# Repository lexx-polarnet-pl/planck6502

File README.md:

# Planck/Lexx W65C02 computer

My custom build of the W65C02 computer, based mostly on the [Planck6502](https://planck6502.com/) hardware design along with several new add-ons.
The firmware has been written entirely from scratch and does not use any of the original Planck code.

The system features a simple DOS-like environment that uses a single CompactFlash (CF) card formatted with a FAT16 partition for storage, enabling seamless file exchange with modern PCs. From the DOS prompt, the user can launch a BASIC interpreter, run a machine-language monitor, or execute custom applications written for the system—much like in MS-DOS.

From a hardware perspective, the computer is equipped with a Pico 2-based video card capable of driving a 640x480 video output with 256 colors. It emulates a VT100 terminal with ANSI color support and provides an 80x30 text mode very similar to standard VGA. The system also features an audio card equipped with a 4-channel, 8-bit DAC for stereo PCM playback, as well as a Yamaha OPL2 chip for FM synthesis.

Mass storage is handled via CF cards, and the base memory (32 KB RAM) is expandable via memory banking. User interaction is supported through standard PS/2 keyboard and mouse interfaces, and an onboard serial interface provides full terminal access as well as file transfer capability.

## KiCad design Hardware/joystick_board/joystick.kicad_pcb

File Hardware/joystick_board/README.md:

## Planck 6502 Joystick Interface

This is the dual joystick interface card for the Planck 6502 computer.

This is an entirely new build, not based on any existing board from the original Planck project.

## Revision History

| Version | Status | Changes |
| :---: | :---: | :--- |
| **1.0** | Under construction | Initial design |

**This board is a work in progress.**

This card aims to be a simple interface between joysticks and the 6502 CPU. The design supports standard Atari DB9 joysticks, extended to support dual fire buttons. The card also features built-in ESD protection.

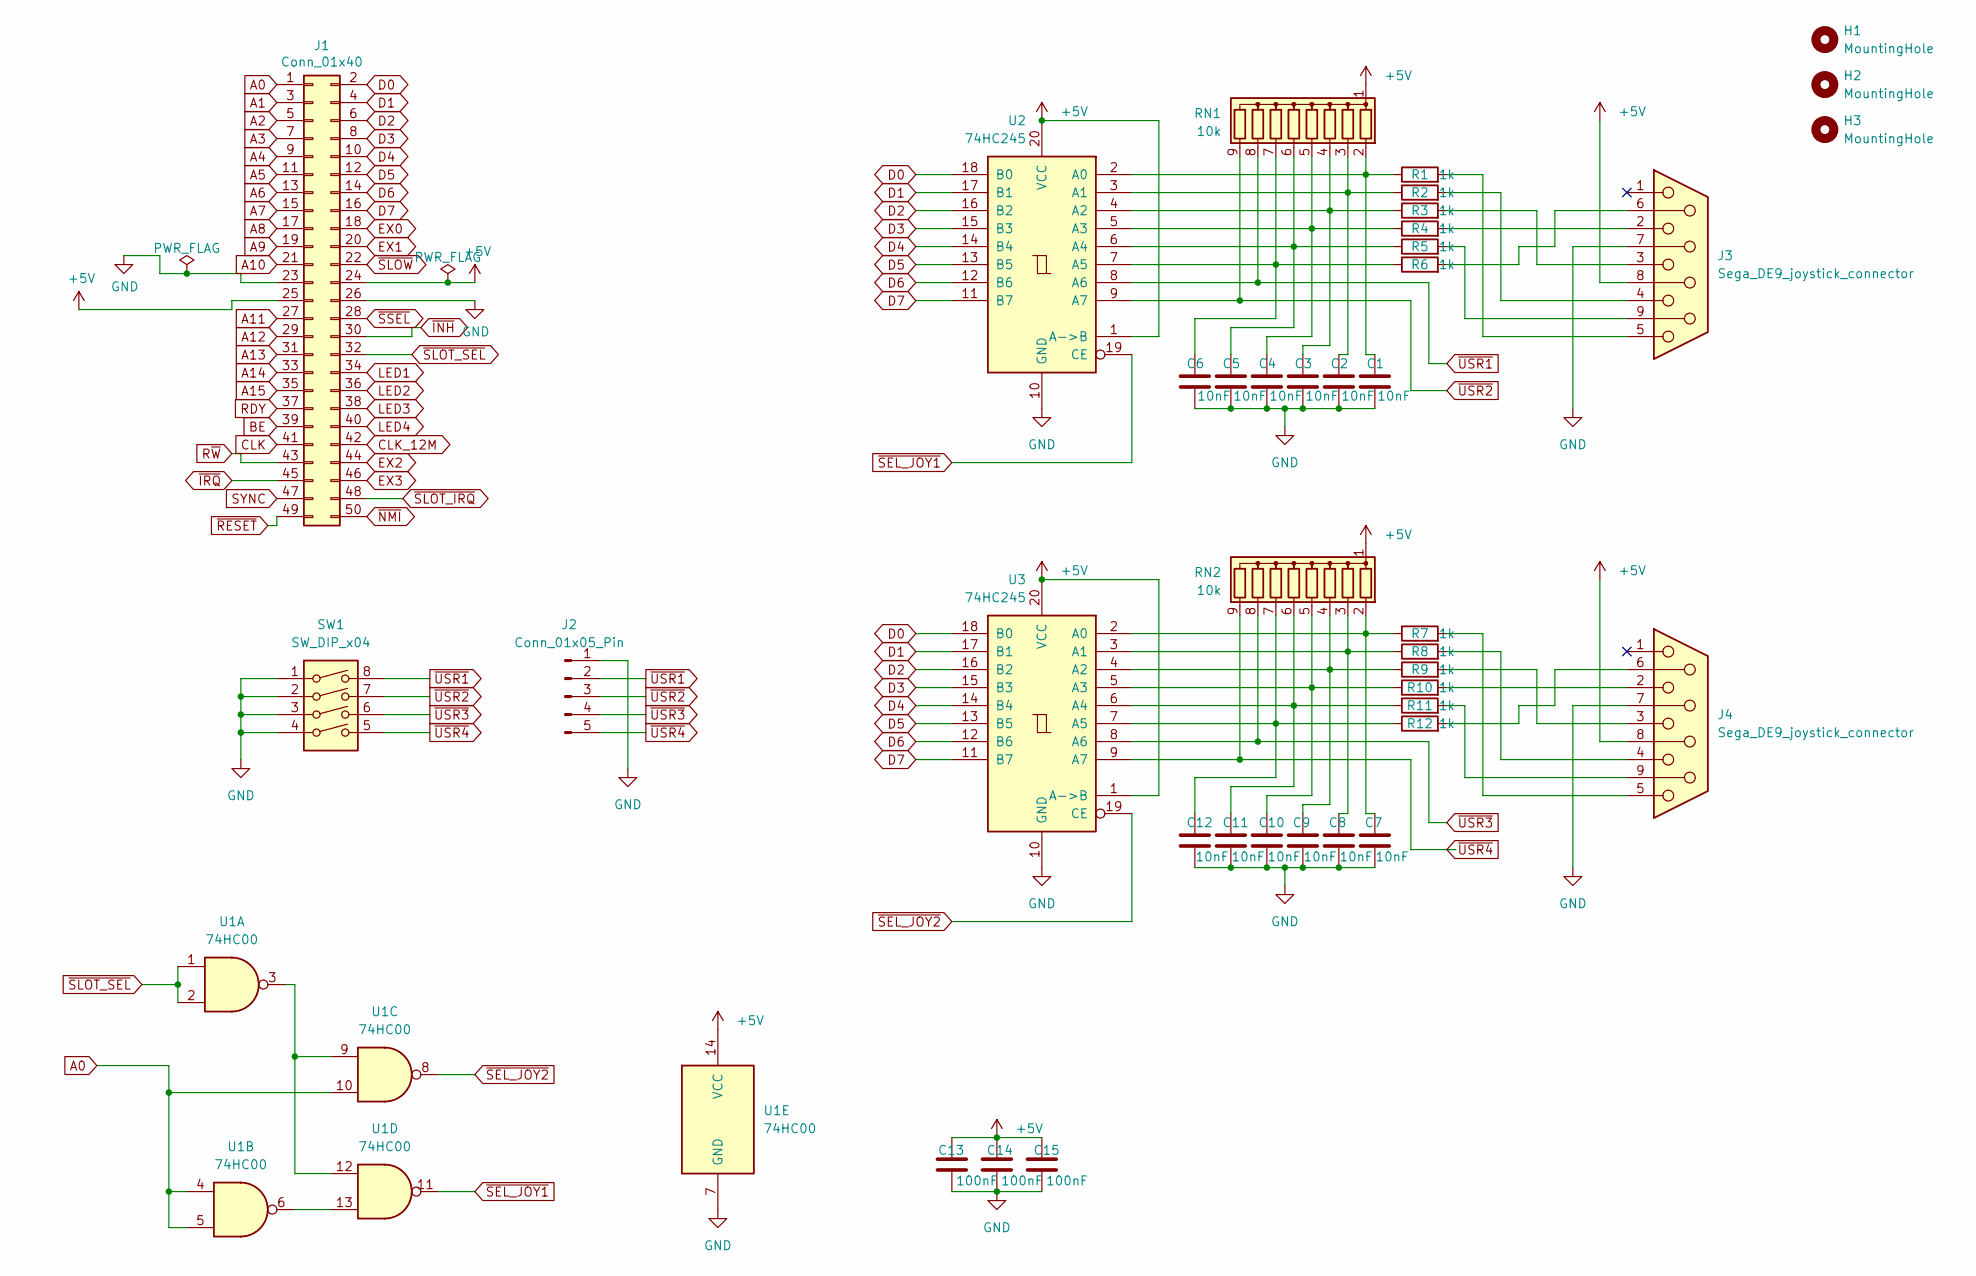
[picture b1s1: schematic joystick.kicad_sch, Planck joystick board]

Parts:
C1, C2, C3, C4, C5, C6, C7, C8, C9, C10, C11, C12: 10nF; C_Disc_D5.0mm_W2.5mm_P5.00mm
C13, C14, C15: 100nF; C_Disc_D5.0mm_W2.5mm_P5.00mm
H1, H2, H3: MountingHole; MountingHole_3.2mm_M3
J1: Conn_01x40; PinHeader_2x25_P2.54mm_Horizontal
J2: Conn_01x05_Pin; PinHeader_1x05_P2.54mm_Vertical
J3, J4: Sega_DE9_joystick_connector; Sega DE9 joystick connector
R1, R2, R3, R4, R5, R6, R7, R8, R9, R10, R11, R12: 1k; R_Axial_DIN0207_L6.3mm_D2.5mm_P2.54mm_Vertical
RN1, RN2: 10k; R_Array_SIP9
SW1: SW_DIP_x04; SW_DIP_SPSTx04_Piano_CTS_Series194-4MSTN_W7.62mm_P2.54mm
U1: 74HC00; DIP-14_W7.62mm_Socket
U2, U3: 74HC245; DIP-20_W7.62mm_Socket

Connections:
+5V: C13.1, C14.1, C15.1, J1.24, J1.25, J3.8, J4.8, RN1.1 (common), RN2.1 (common), U1.14 (VCC), U2.1 (A->B), U2.20 (VCC), U3.1 (A->B), U3.20 (VCC)
A0: J1.1, U1.4, U1.5, U1.10
A1: J1.3
A2: J1.5
A3: J1.7
A4: J1.9
A5: J1.11
A6: J1.13
A7: J1.15
A8: J1.17
A9: J1.19
A10: J1.21
A11: J1.27
A12: J1.29
A13: J1.31
A14: J1.33
A15: J1.35
BE: J1.39
CLK: J1.41
CLK_12M: J1.42
D0: J1.2, U2.18 (B0), U3.18 (B0)
D1: J1.4, U2.17 (B1), U3.17 (B1)
D2: J1.6, U2.16 (B2), U3.16 (B2)
D3: J1.8, U2.15 (B3), U3.15 (B3)
D4: J1.10, U2.14 (B4), U3.14 (B4)
D5: J1.12, U2.13 (B5), U3.13 (B5)
D6: J1.14, U2.12 (B6), U3.12 (B6)
D7: J1.16, U2.11 (B7), U3.11 (B7)
EX0: J1.18
EX1: J1.20
EX2: J1.44
EX3: J1.46
GND: C1.2, C2.2, C3.2, C4.2, C5.2, C6.2, C7.2, C8.2, C9.2, C10.2, C11.2, C12.2, C13.2, C14.2, C15.2, J1.23, J1.26, J2.1, J3.7, J4.7, SW1.1, SW1.2, SW1.3, SW1.4, U1.7 (GND), U2.10 (GND), U3.10 (GND)
LED1: J1.34
LED2: J1.36
LED3: J1.38
LED4: J1.40
unnamed: J3.2, R4.2
unnamed: J3.3, R3.2
unnamed: J3.4, R2.2
unnamed: J3.5, R1.2
unnamed: J3.6, R6.2
unnamed: J3.9, R5.2
unnamed: J4.2, R10.2
unnamed: J4.3, R9.2
unnamed: J4.4, R8.2
unnamed: J4.5, R7.2
unnamed: J4.6, R12.2
unnamed: J4.9, R11.2
unnamed: C1.1, R1.1, RN1.2 (R1), U2.2 (A0)
unnamed: C2.1, R2.1, RN1.3 (R2), U2.3 (A1)
unnamed: C3.1, R3.1, RN1.4 (R3), U2.4 (A2)
unnamed: C4.1, R4.1, RN1.5 (R4), U2.5 (A3)
unnamed: C5.1, R5.1, RN1.6 (R5), U2.6 (A4)
unnamed: C6.1, R6.1, RN1.7 (R6), U2.7 (A5)
unnamed: C7.1, R7.1, RN2.2 (R1), U3.2 (A0)
unnamed: C8.1, R8.1, RN2.3 (R2), U3.3 (A1)
unnamed: C9.1, R9.1, RN2.4 (R3), U3.4 (A2)
unnamed: C10.1, R10.1, RN2.5 (R4), U3.5 (A3)
unnamed: C11.1, R11.1, RN2.6 (R5), U3.6 (A4)
unnamed: C12.1, R12.1, RN2.7 (R6), U3.7 (A5)
unnamed: U1.3, U1.9, U1.12
unnamed: U1.6, U1.13
RDY: J1.37
R~W: J1.43
SYNC: J1.47
~INH: J1.30
~IRQ: J1.45
~NMI: J1.50
~RESET: J1.49
~SEL_JOY1: U1.11, U2.19 (CE)
~SEL_JOY2: U1.8, U3.19 (CE)
~SLOT_IRQ: J1.48
~SLOT_SEL: J1.32, U1.1, U1.2
~SLOW: J1.22
~SSEL: J1.28
~USR1: J2.2, RN1.8 (R7), SW1.8, U2.8 (A6)
~USR2: J2.3, RN1.9 (R8), SW1.7, U2.9 (A7)
~USR3: J2.4, RN2.8 (R7), SW1.6, U3.8 (A6)
~USR4: J2.5, RN2.9 (R8), SW1.5, U3.9 (A7)

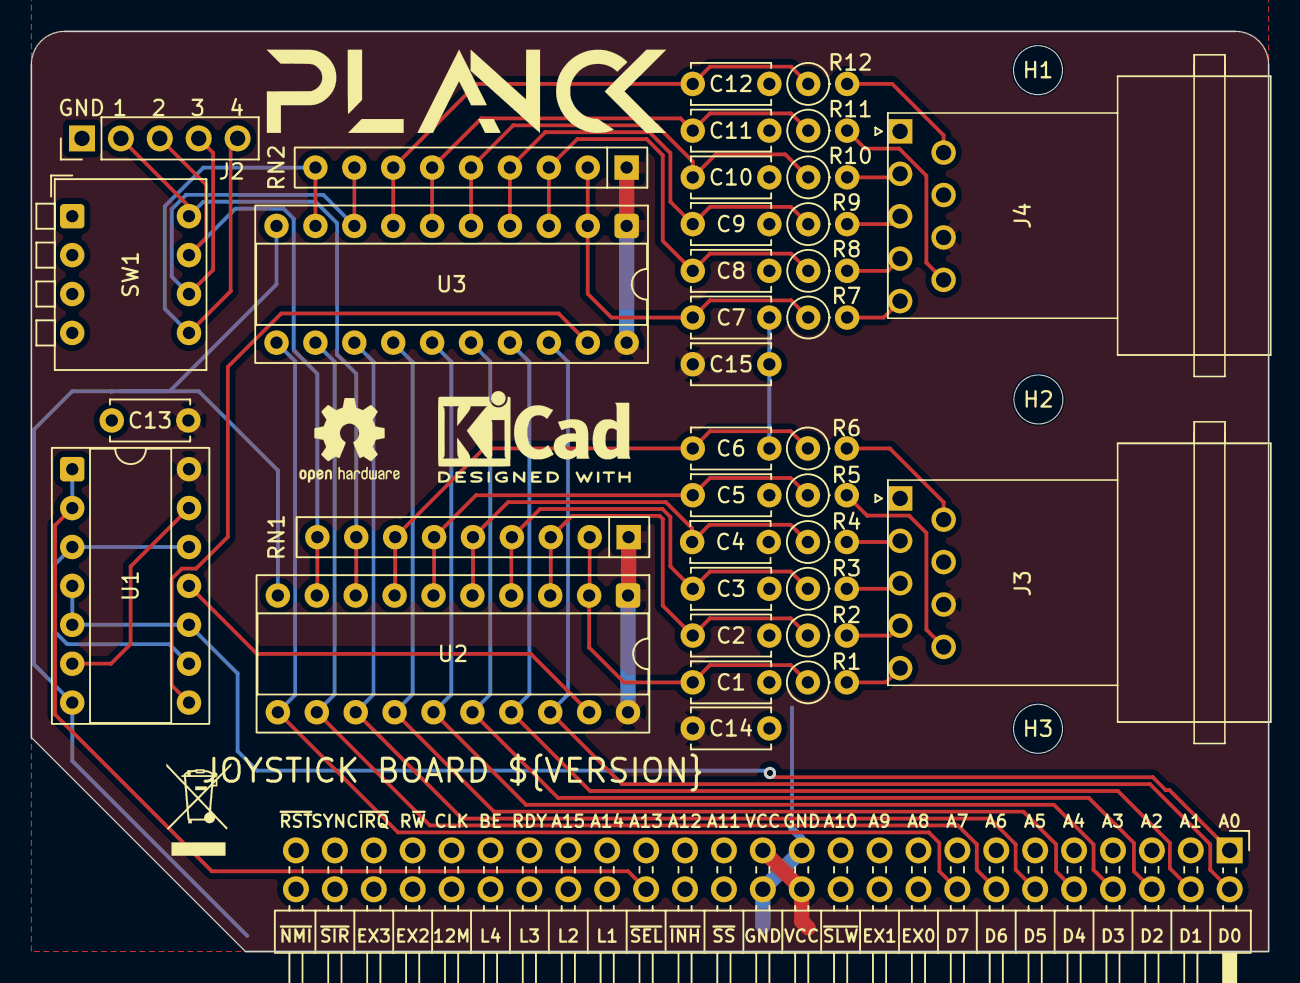
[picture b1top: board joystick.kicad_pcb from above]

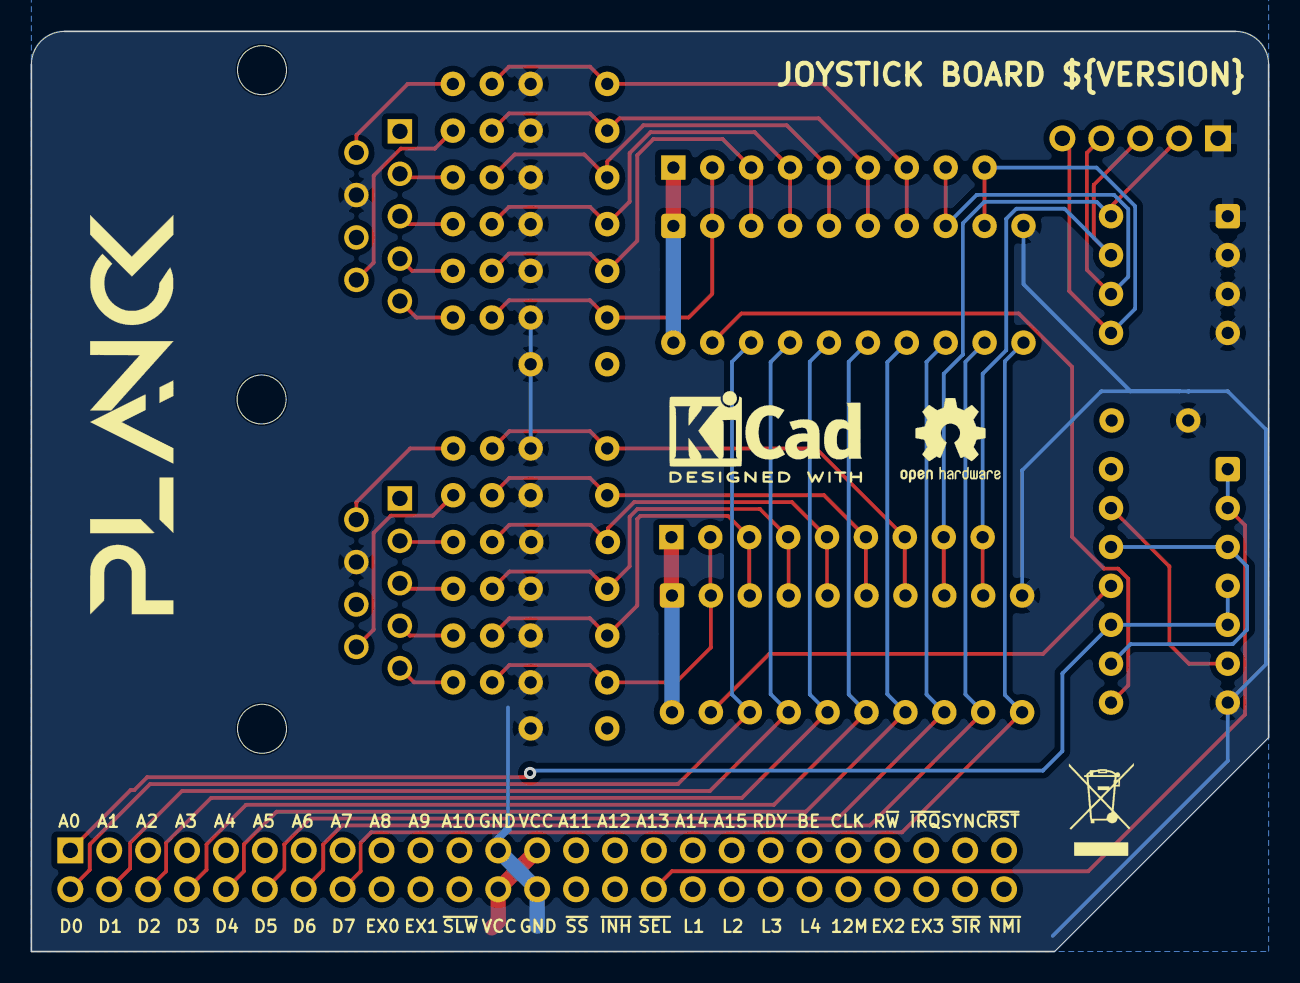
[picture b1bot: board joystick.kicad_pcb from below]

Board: 2 copper layers, 80.8 x 60.1 mm, 48 parts (4 on the bottom side), 44 nets.

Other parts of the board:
KICADLOGO1, KICADLOGO2: KiCad-Logo2_5mm_SilkScreen
LOGO1, LOGO2: LOGO; logo
OPENHARDWARE1, OPENHARDWARE2: OSHW-Logo2_7.3x6mm_SilkScreen
WASTE1, WASTE2: WEEE-Logo_4.2x6mm_SilkScreen

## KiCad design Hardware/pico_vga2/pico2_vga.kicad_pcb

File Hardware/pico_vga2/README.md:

## Planck 6502 Pico 2 VGA Board 

This is a VGA board for the Planck 6502 computer, based on the Raspberry Pi Pico 2. 

> [!CAUTION]
> **Compatibility Warning:**  
> This version is **not** compatible with the 1st generation Pico, as it is not 5V tolerant. **Use the Pico 2 only**, otherwise you risk damaging the board.

Compared to the original design, this card was rebuilt from scratch to achieve three main goals:
1. **PicoVGA Compatibility:** The pinout and resistor ladder match the [PicoVGA cmake](https://github.com/codaris/picovga-cmake) project, making the library as simple as possible to use.
2. **Hardware RDY Latch:** Implemented to give the Pico enough time to read, process, and respond to the W65C02 CPU by utilizing the RDY signal to pause the CPU when needed.
3. **Optimized Bus Routing:** The Address and Data bus pinout order was reversed to enable faster and more efficient bus operations on the Pico. 

Additionally, by leveraging the Pico 2, SMD level shifters were removed, leaving only a single THT bus buffer on the PCB. As a result, the entire board can now be soldered using strictly Through-Hole (THT) components.

## Revision History

| Version | Status | Changes |
| :---: | :---: | :--- |
| **1.0** | Work in progress | Initial design |

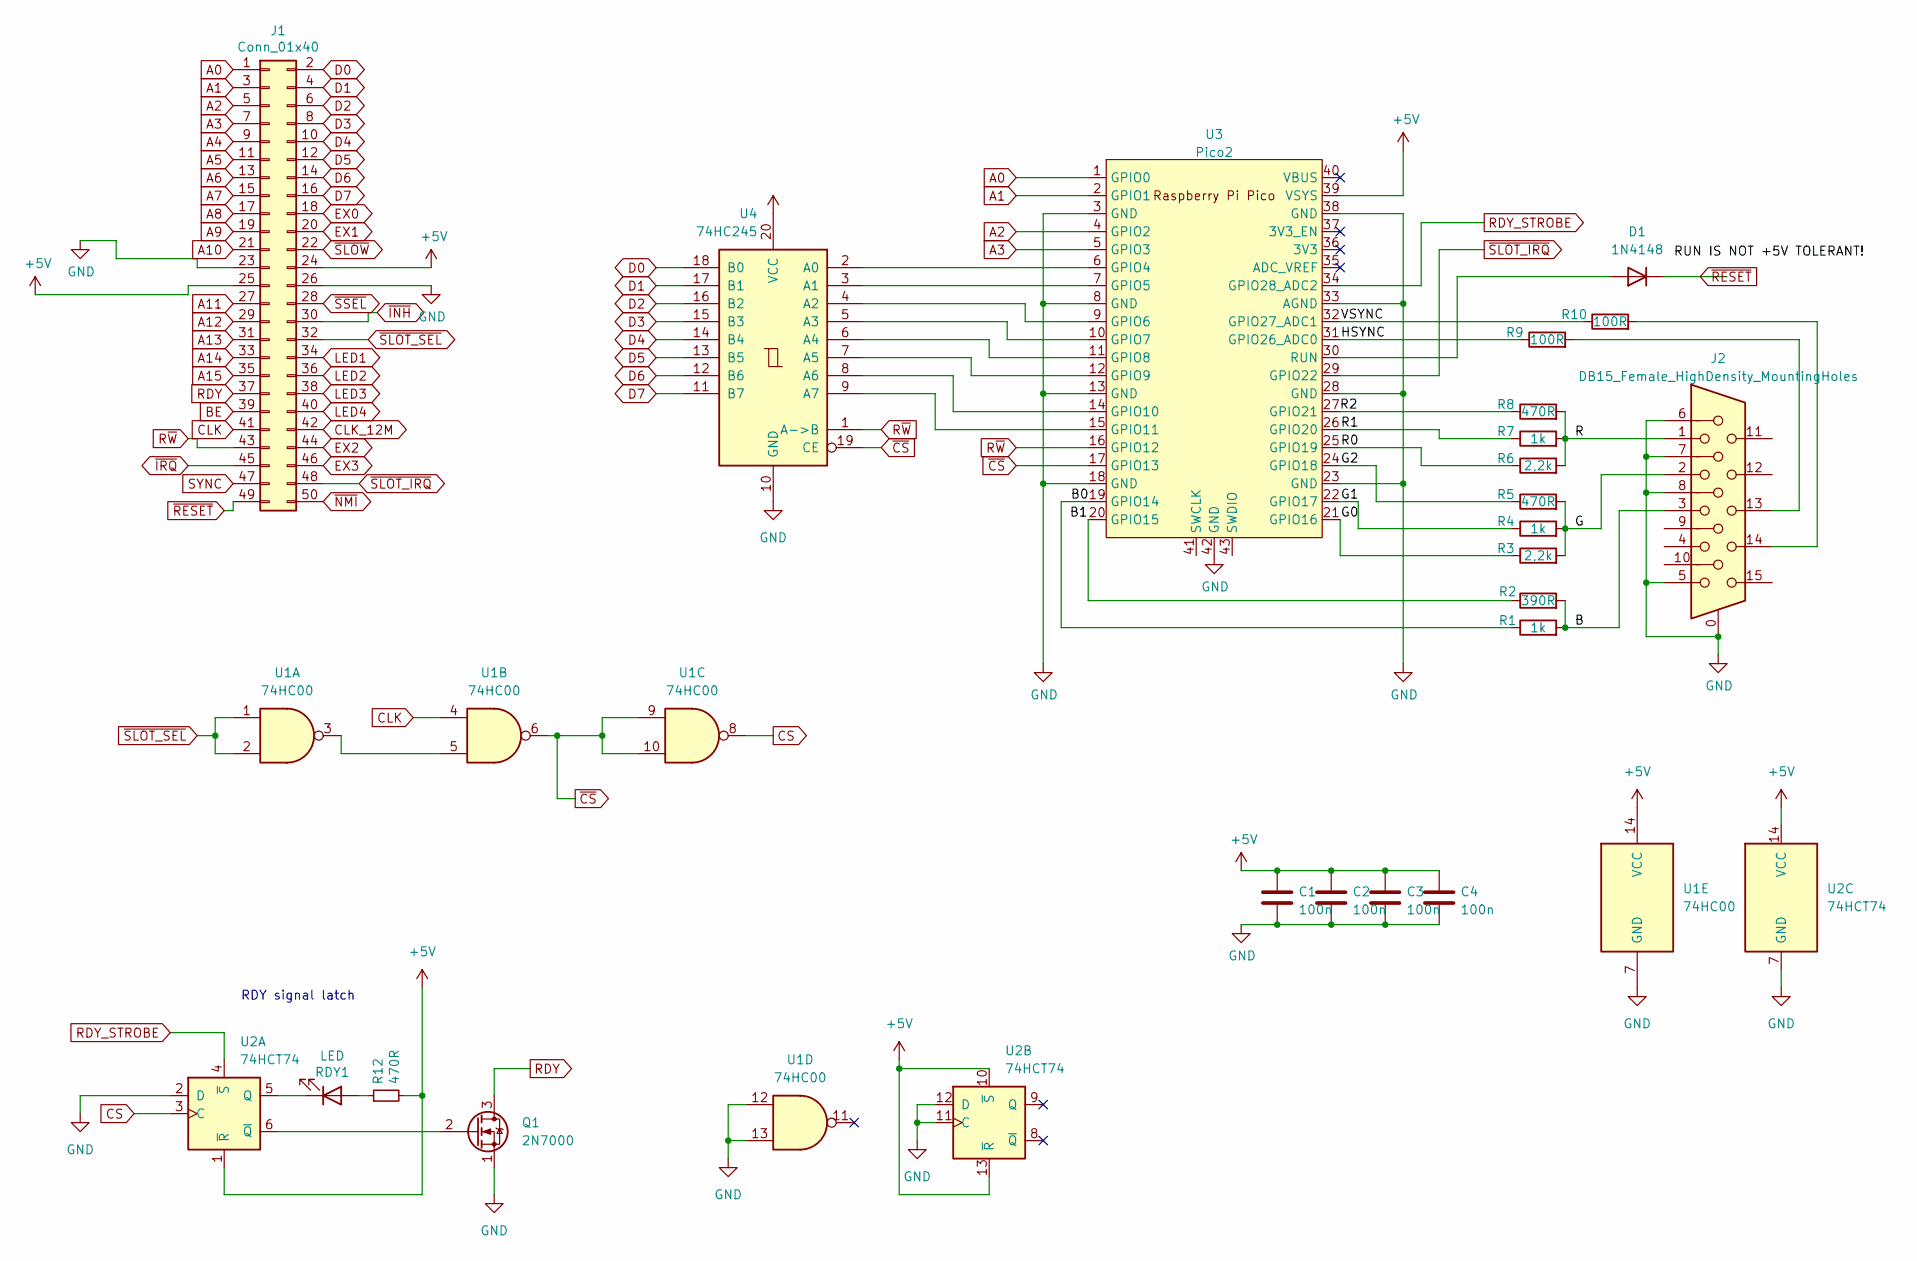
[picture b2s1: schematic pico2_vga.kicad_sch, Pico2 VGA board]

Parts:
C1, C2, C3, C4: 100n; C_Disc_D5.0mm_W2.5mm_P5.00mm
D1: 1N4148; D_DO-35_SOD27_P7.62mm_Horizontal
J1: Conn_01x40; PinHeader_2x25_P2.54mm_Horizontal
J2: DB15_Female_HighDensity_MountingHoles; DSUB-15-HD_Socket_Horizontal_P2.29x1.90mm_EdgePinOffset3.03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
Q1: 2N7000; TO-92_Inline
R1, R4, R7: 1k; R_Axial_DIN0309_L9.0mm_D3.2mm_P2.54mm_Vertical
R2: 390R; R_Axial_DIN0309_L9.0mm_D3.2mm_P2.54mm_Vertical
R3, R6: 2,2k; R_Axial_DIN0309_L9.0mm_D3.2mm_P2.54mm_Vertical
R5, R8: 470R; R_Axial_DIN0309_L9.0mm_D3.2mm_P2.54mm_Vertical
R9, R10: 100R; R_Axial_DIN0309_L9.0mm_D3.2mm_P2.54mm_Vertical
R12: 470R; R_Axial_DIN0207_L6.3mm_D2.5mm_P10.16mm_Horizontal
RDY1: LED; LED_D3.0mm
U1: 74HC00; DIP-14_W7.62mm_Socket
U2: 74HCT74; DIP-14_W7.62mm_Socket
U3: Pico2; RPi_Pico_SMD_TH
U4: 74HC245; DIP-20_W7.62mm_Socket

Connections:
+5V: C1.1, C2.1, C3.1, C4.1, J1.24, J1.25, R12.2, U1.14 (VCC), U2.1 (~R), U2.10 (~S), U2.13 (~R), U2.14 (VCC), U3.39 (VSYS), U4.20 (VCC)
/B: J2.3, R1.2, R2.2
/B0: R1.1, U3.19 (GPIO14)
/B1: R2.1, U3.20 (GPIO15)
/G: J2.2, R3.2, R4.2, R5.2
/G0: R3.1, U3.21 (GPIO16)
/G1: R4.1, U3.22 (GPIO17)
/G2: R5.1, U3.24 (GPIO18)
/HSYNC: R9.1, U3.31 (GPIO26_ADC0)
/R: J2.1, R6.2, R7.2, R8.2
/R0: R6.1, U3.25 (GPIO19)
/R1: R7.1, U3.26 (GPIO20)
/R2: R8.1, U3.27 (GPIO21)
/VSYNC: R10.1, U3.32 (GPIO27_ADC1)
A0: J1.1, U3.1 (GPIO0)
A1: J1.3, U3.2 (GPIO1)
A2: J1.5, U3.4 (GPIO2)
A3: J1.7, U3.5 (GPIO3)
A4: J1.9
A5: J1.11
A6: J1.13
A7: J1.15
A8: J1.17
A9: J1.19
A10: J1.21
A11: J1.27
A12: J1.29
A13: J1.31
A14: J1.33
A15: J1.35
BE: J1.39
CLK: J1.41, U1.4
CLK_12M: J1.42
CS: U1.8, U2.3 (C)
D0: J1.2, U4.18 (B0)
D1: J1.4, U4.17 (B1)
D2: J1.6, U4.16 (B2)
D3: J1.8, U4.15 (B3)
D4: J1.10, U4.14 (B4)
D5: J1.12, U4.13 (B5)
D6: J1.14, U4.12 (B6)
D7: J1.16, U4.11 (B7)
EX0: J1.18
EX1: J1.20
EX2: J1.44
EX3: J1.46
GND: C1.2, C2.2, C3.2, C4.2, J1.23, J1.26, J2.0, J2.5, J2.6, J2.7, J2.8, Q1.1 (S), U1.7 (GND), U1.12, U1.13, U2.2 (D), U2.7 (GND), U2.11 (C), U2.12 (D), U3.3 (GND), U3.8 (GND), U3.13 (GND), U3.18 (GND), U3.23 (GND), U3.28 (GND), U3.33 (AGND), U3.38 (GND), U3.42 (GND), U4.10 (GND)
LED1: J1.34
LED2: J1.36
LED3: J1.38
LED4: J1.40
unnamed: D1.2 (A), U3.30 (RUN)
unnamed: J2.13, R9.2
unnamed: J2.14, R10.2
unnamed: Q1.2 (G), U2.6 (~Q)
unnamed: R12.1, RDY1.2 (A)
unnamed: RDY1.1 (K), U2.5 (Q)
unnamed: U1.3, U1.5
unnamed: U3.6 (GPIO4), U4.2 (A0)
unnamed: U3.7 (GPIO5), U4.3 (A1)
unnamed: U3.9 (GPIO6), U4.4 (A2)
unnamed: U3.10 (GPIO7), U4.5 (A3)
unnamed: U3.11 (GPIO8), U4.6 (A4)
unnamed: U3.12 (GPIO9), U4.7 (A5)
unnamed: U3.14 (GPIO10), U4.8 (A6)
unnamed: U3.15 (GPIO11), U4.9 (A7)
RDY: J1.37, Q1.3 (D)
RDY_STROBE: U2.4 (~S), U3.34 (GPIO28_ADC2)
R~W: J1.43, U3.16 (GPIO12), U4.1 (A->B)
SYNC: J1.47
~CS: U1.6, U1.9, U1.10, U3.17 (GPIO13), U4.19 (CE)
~INH: J1.30
~IRQ: J1.45
~NMI: J1.50
~RESET: D1.1 (K), J1.49
~SLOT_IRQ: J1.48, U3.29 (GPIO22)
~SLOT_SEL: J1.32, U1.1, U1.2
~SLOW: J1.22
~SSEL: J1.28

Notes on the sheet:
RDY signal latch

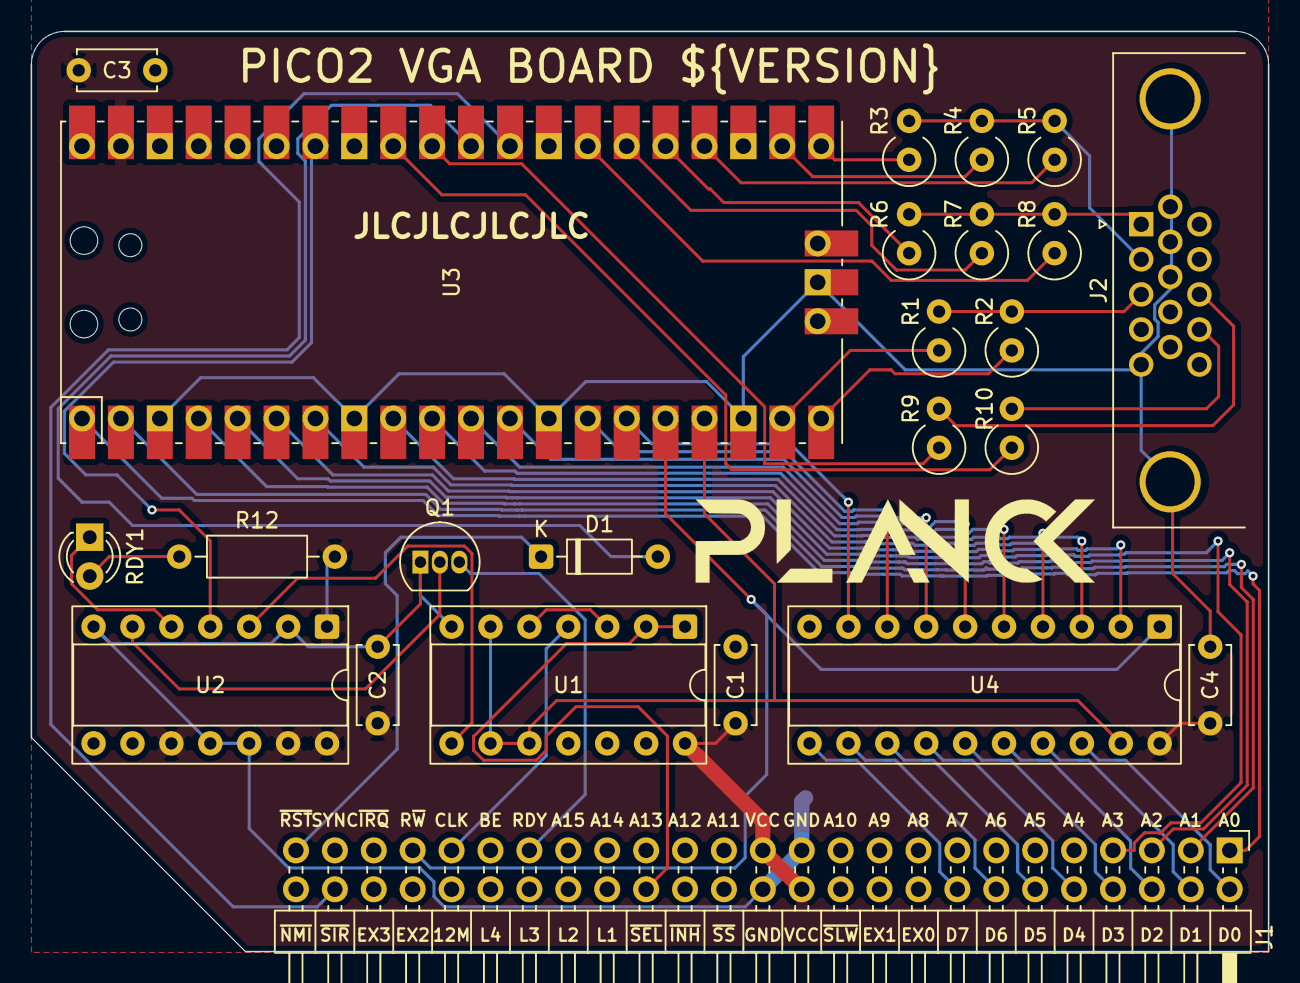
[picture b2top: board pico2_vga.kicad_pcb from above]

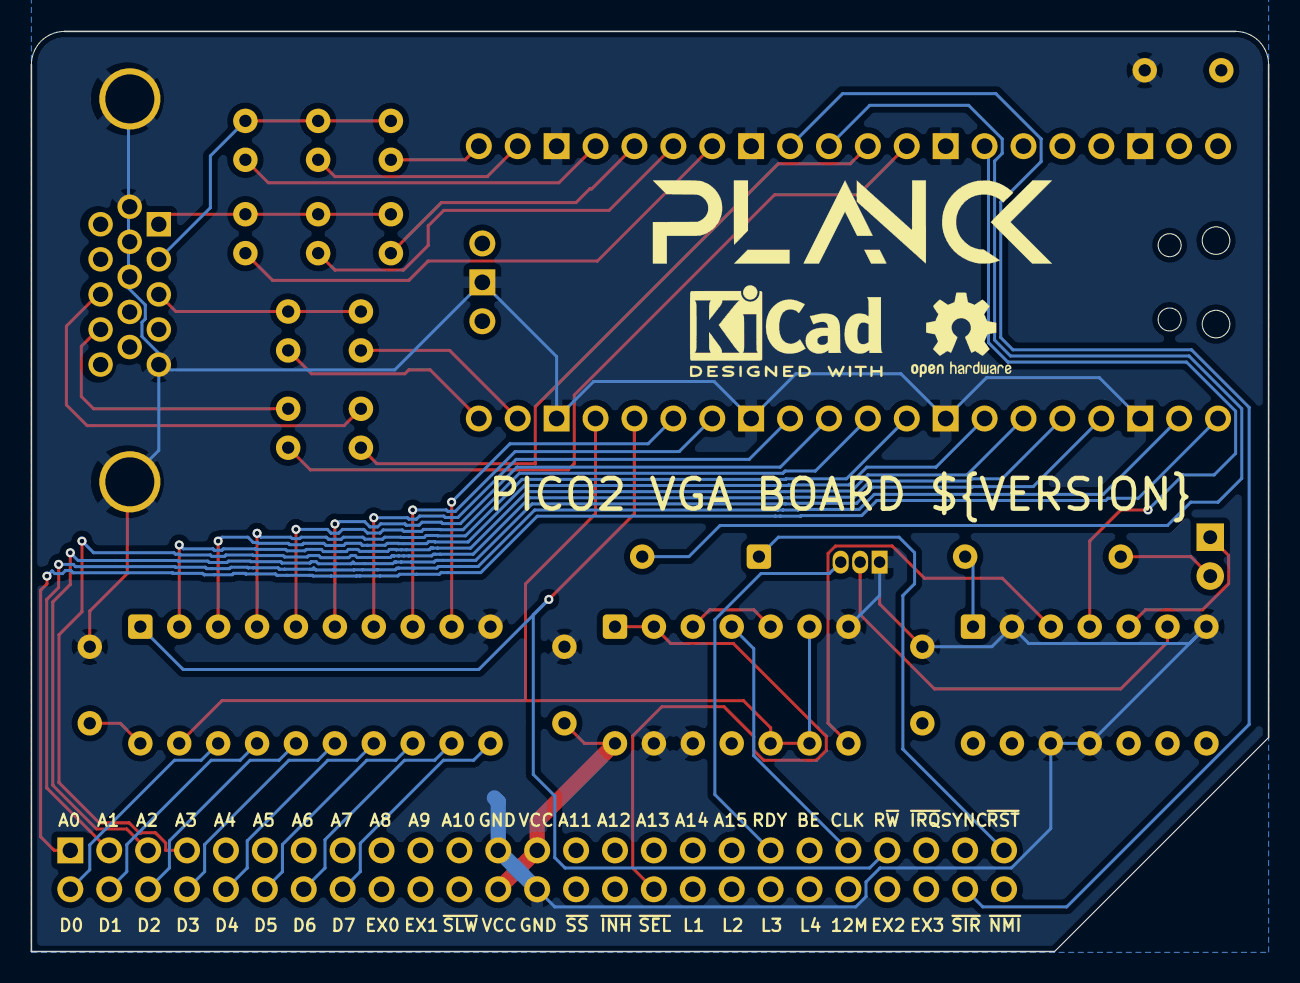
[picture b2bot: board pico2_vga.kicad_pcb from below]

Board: 2 copper layers, 80.8 x 60.1 mm, 28 parts (3 on the bottom side), 51 nets.

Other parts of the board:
KICAD1: KiCad-Logo2_5mm_SilkScreen
LOGO1, LOGO1#2: LOGO; logo
OSHW1: OSHW-Logo2_7.3x6mm_SilkScreen

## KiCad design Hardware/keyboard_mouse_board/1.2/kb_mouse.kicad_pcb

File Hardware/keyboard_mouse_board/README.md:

## Planck 6502 Keyboard and Mouse Interface

This is the keyboard and mouse interface card for the Planck 6502 computer.

This is an entirely new build, not based on any existing board from the original Planck project.

## Revision History

| Version | Status | Changes |
| :---: | :---: | :--- |
| **1.2** | Work in progress | RDY latch improvements to support multiple cards using the RDY signal on the bus (open-collector configuration) |
| **1.1** | Work in progress | RDY latch corrected, CS signal routed to ATmega |
| **1.0** | Not working | Initial design |

**Version 1.0 doesn't work correctly, version 1.1 was not tested yet**

This card was designed to act as an abstraction layer between a keyboard/mouse and the W65C02 CPU. It uses an ATmega328P microcontroller to handle all the signal translation. From the CPU's perspective, the entire card is accessible within a 16-byte memory block, and all communication is handled simply by reading from or writing to memory.

Because the ATmega may be too slow to respond directly to the CPU (which is the case when running the Planck at 12 MHz against the ATmega at 8 MHz), the card includes 74-series logic circuitry. This logic pulls the RDY line low immediately when the SLOT_SEL signal is detected, effectively pausing the CPU. Once the ATmega finishes processing the request and the data is ready, it generates a strobe signal (RDY_STROBE) to release the latch, allowing the CPU to resume execution. Note that due to this design, the card may not work with an original 6502 CPU, which handles the RDY line differently. However, since the Planck uses the W65C02, it works reliably.

The board is equipped with two PS/2 ports for connecting a keyboard and mouse, as well as a DS1307+ RTC chip with a CR2032 battery holder to provide real-time clock functionality. It also features an ISP header to flash the ATmega without removing it from the socket. Since the ISP lines are shared with the PS/2 ports, any connected PS/2 devices must be unplugged during flashing to avoid failure.

For operational details, memory mapping, and documentation, please refer to the firmware folder for this card.

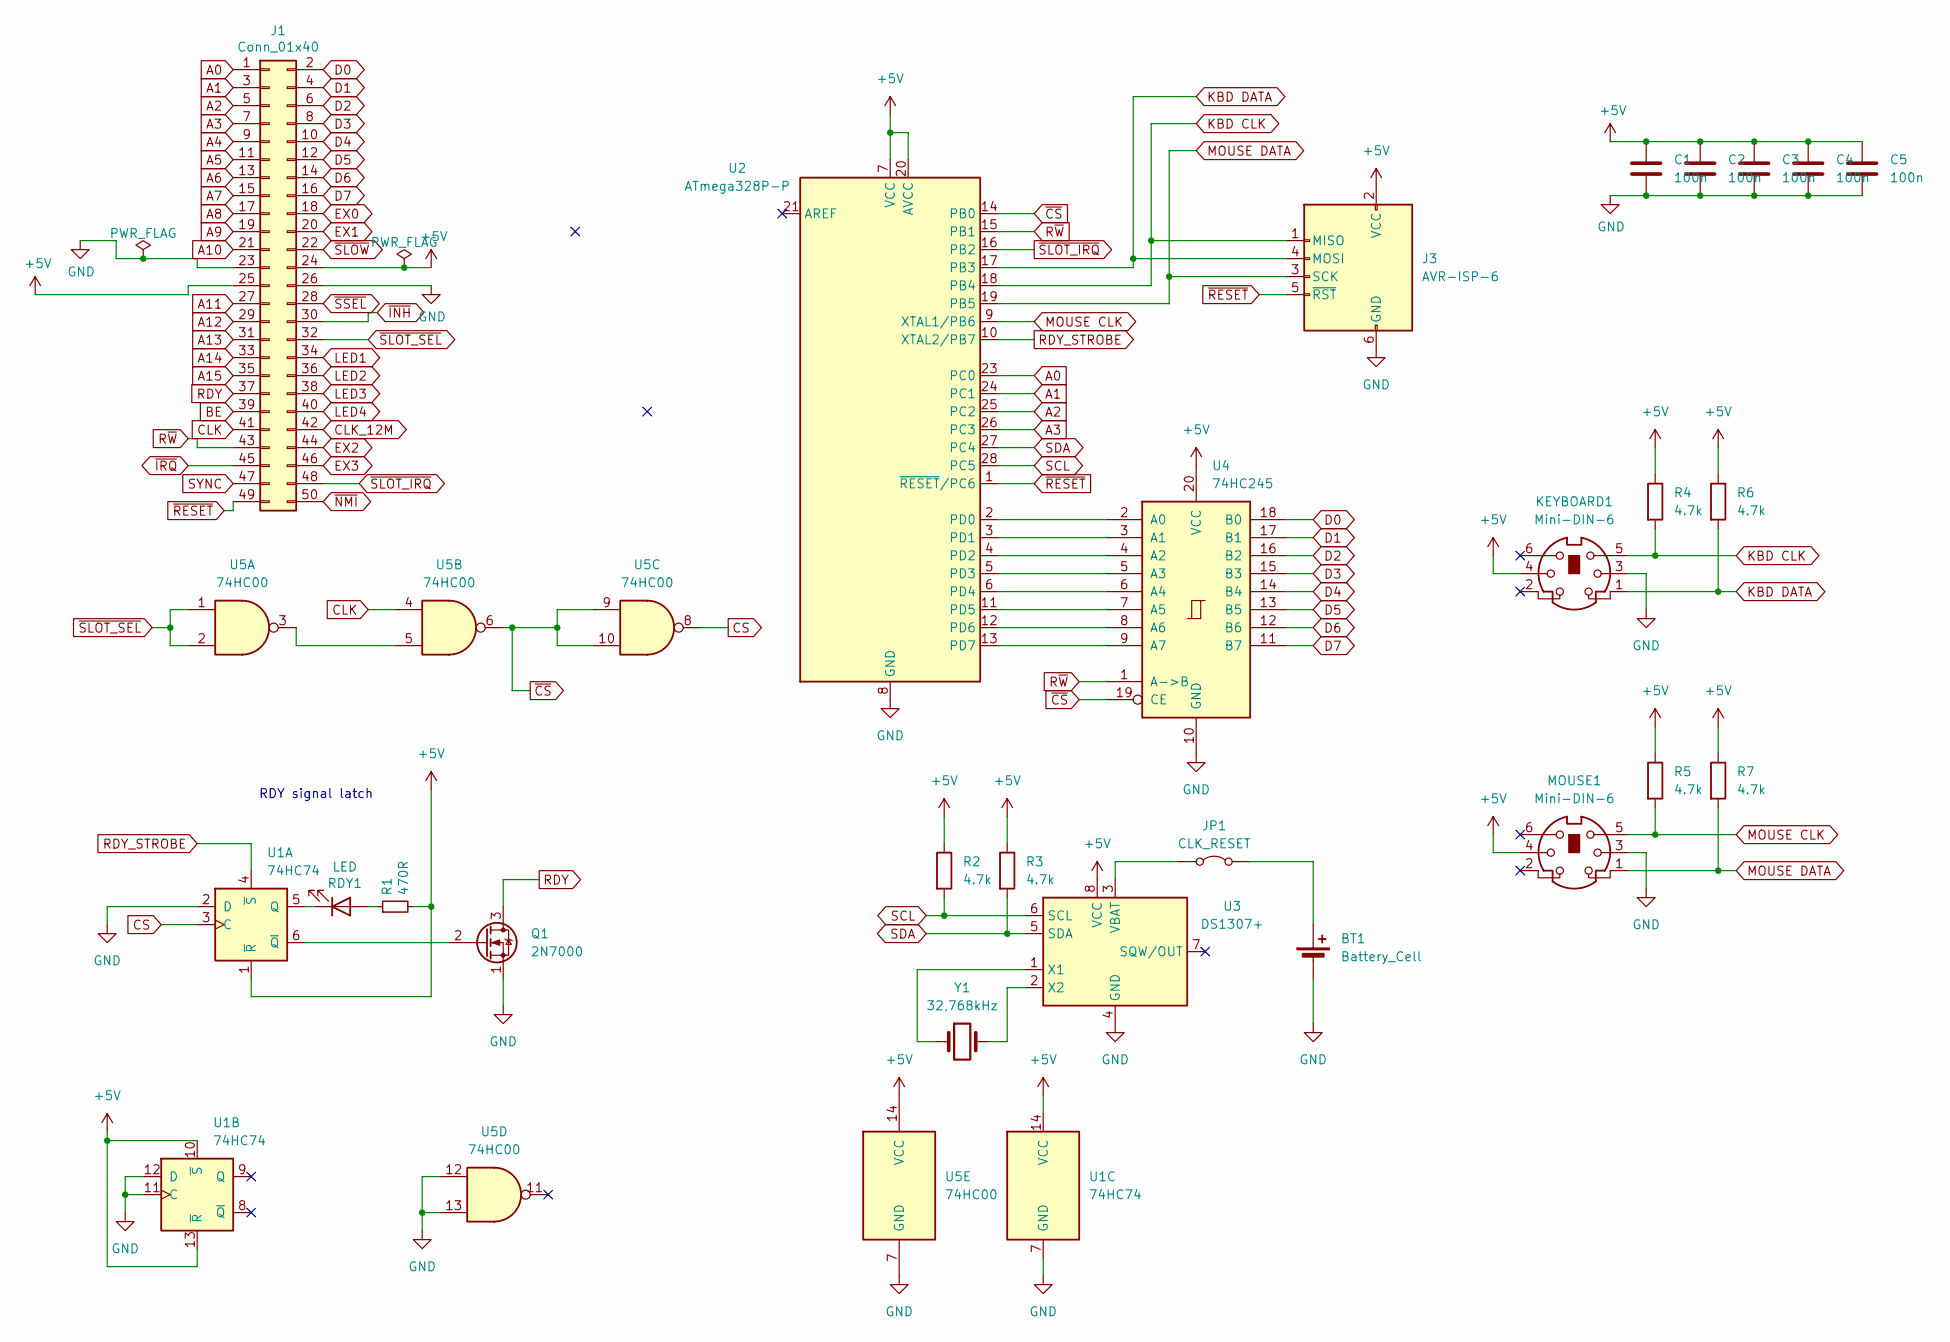
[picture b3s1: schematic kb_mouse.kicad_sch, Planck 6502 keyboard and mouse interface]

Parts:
BT1: Battery_Cell; BatteryHolder_MYOUNG_BS-07-A1BJ001_CR2032
C1, C2, C3, C4, C5: 100n; C_Disc_D5.0mm_W2.5mm_P5.00mm
J1: Conn_01x40; PinHeader_2x25_P2.54mm_Horizontal
J3: AVR-ISP-6; IDC-Header_2x03_P2.54mm_Horizontal
JP1: CLK_RESET; PinHeader_1x02_P2.54mm_Vertical
KEYBOARD1: Mini-DIN-6; Connector_Mini-DIN_Female_6Pin_2rows
MOUSE1: Mini-DIN-6; Connector_Mini-DIN_Female_6Pin_2rows
Q1: 2N7000; TO-92_Inline
R1: 470R; R_Axial_DIN0207_L6.3mm_D2.5mm_P10.16mm_Horizontal
R2, R3, R4, R5, R6, R7: 4.7k; R_Axial_DIN0207_L6.3mm_D2.5mm_P10.16mm_Horizontal
RDY1: LED; LED_D3.0mm
U1: 74HC74; DIP-14_W7.62mm_Socket
U2: ATmega328P-P; DIP-28_W7.62mm_Socket
U3: DS1307+; DIP-8_W7.62mm_Socket
U4: 74HC245; DIP-20_W7.62mm_Socket
U5: 74HC00; DIP-14_W7.62mm_Socket
Y1: 32,768kHz; Crystal_DS15_D1.5mm_L5.0mm_Horizontal_1EP_style2

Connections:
+5V: C1.1, C2.1, C3.1, C4.1, C5.1, J1.24, J1.25, J3.2 (VCC), KEYBOARD1.4, MOUSE1.4, R1.2, R2.1, R3.1, R4.1, R5.1, R6.1, R7.1, U1.1 (~R), U1.10 (~S), U1.13 (~R), U1.14 (VCC), U2.7 (VCC), U2.20 (AVCC), U3.8 (VCC), U4.20 (VCC), U5.14 (VCC); also elsewhere on the board
A0: J1.1, U2.23 (PC0)
A1: J1.3, U2.24 (PC1)
A2: J1.5, U2.25 (PC2)
A3: J1.7, U2.26 (PC3)
A4: J1.9
A5: J1.11
A6: J1.13
A7: J1.15
A8: J1.17
A9: J1.19
A10: J1.21
A11: J1.27
A12: J1.29
A13: J1.31
A14: J1.33
A15: J1.35
BE: J1.39
CLK: J1.41, U5.4
CLK_12M: J1.42
CS: U1.3 (C), U5.8
D0: J1.2, U4.18 (B0)
D1: J1.4, U4.17 (B1)
D2: J1.6, U4.16 (B2)
D3: J1.8, U4.15 (B3)
D4: J1.10, U4.14 (B4)
D5: J1.12, U4.13 (B5)
D6: J1.14, U4.12 (B6)
D7: J1.16, U4.11 (B7)
EX0: J1.18
EX1: J1.20
EX2: J1.44
EX3: J1.46
GND: BT1.2 (-), C1.2, C2.2, C3.2, C4.2, C5.2, J1.23, J1.26, J3.6 (GND), KEYBOARD1.3, MOUSE1.3, Q1.1 (S), U1.2 (D), U1.7 (GND), U1.11 (C), U1.12 (D), U2.8 (GND), U2.22 (GND), U3.4 (GND), U4.10 (GND), U5.7 (GND), U5.12, U5.13; also elsewhere on the board
KBD CLK: J3.1 (MISO), KEYBOARD1.5, R4.2, U2.18 (PB4); also elsewhere on the board
KBD DATA: J3.4 (MOSI), KEYBOARD1.1, R6.2, U2.17 (PB3); also elsewhere on the board
LED1: J1.34
LED2: J1.36
LED3: J1.38
LED4: J1.40
MOUSE CLK: MOUSE1.5, R5.2, U2.9 (XTAL1/PB6); also elsewhere on the board
MOUSE DATA: J3.3 (SCK), MOUSE1.1, R7.2, U2.19 (PB5); also elsewhere on the board
unnamed: BT1.1 (+), JP1.2 (B)
unnamed: JP1.1 (A), U3.3 (VBAT)
unnamed: Q1.2 (G), U1.6 (~Q)
unnamed: R1.1, RDY1.2 (A)
unnamed: RDY1.1 (K), U1.5 (Q)
unnamed: U2.2 (PD0), U4.2 (A0)
unnamed: U2.3 (PD1), U4.3 (A1)
unnamed: U2.4 (PD2), U4.4 (A2)
unnamed: U2.5 (PD3), U4.5 (A3)
unnamed: U2.6 (PD4), U4.6 (A4)
unnamed: U2.11 (PD5), U4.7 (A5)
unnamed: U2.12 (PD6), U4.8 (A6)
unnamed: U2.13 (PD7), U4.9 (A7)
unnamed: U3.1 (X1), Y1.1
unnamed: U3.2 (X2), Y1.2
unnamed: U5.3, U5.5
RDY: J1.37, Q1.3 (D)
RDY_STROBE: U1.4 (~S), U2.10 (XTAL2/PB7); also elsewhere on the board
R~W: J1.43, U2.15 (PB1), U4.1 (A->B)
SCL: R2.2, U2.28 (PC5), U3.6 (SCL)
SDA: R3.2, U2.27 (PC4), U3.5 (SDA)
SYNC: J1.47
~CS: U2.14 (PB0), U4.19 (CE), U5.6, U5.9, U5.10
~INH: J1.30
~IRQ: J1.45
~NMI: J1.50
~RESET: J1.49, J3.5 (~RST), U2.1 (~RESET/PC6)
~SLOT_IRQ: J1.48, U2.16 (PB2)
~SLOT_SEL: J1.32, U5.1, U5.2
~SLOW: J1.22
~SSEL: J1.28

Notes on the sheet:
RDY signal latch

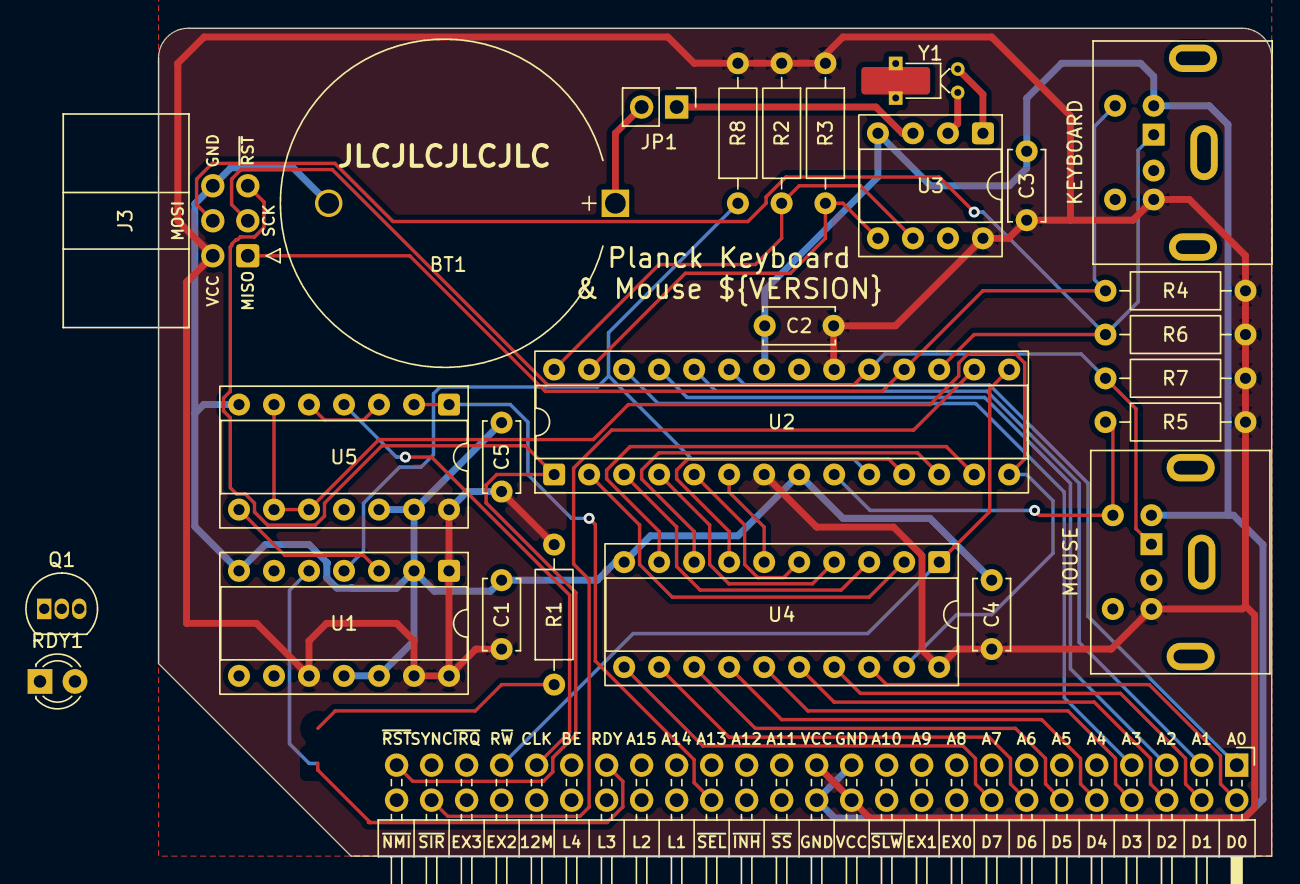
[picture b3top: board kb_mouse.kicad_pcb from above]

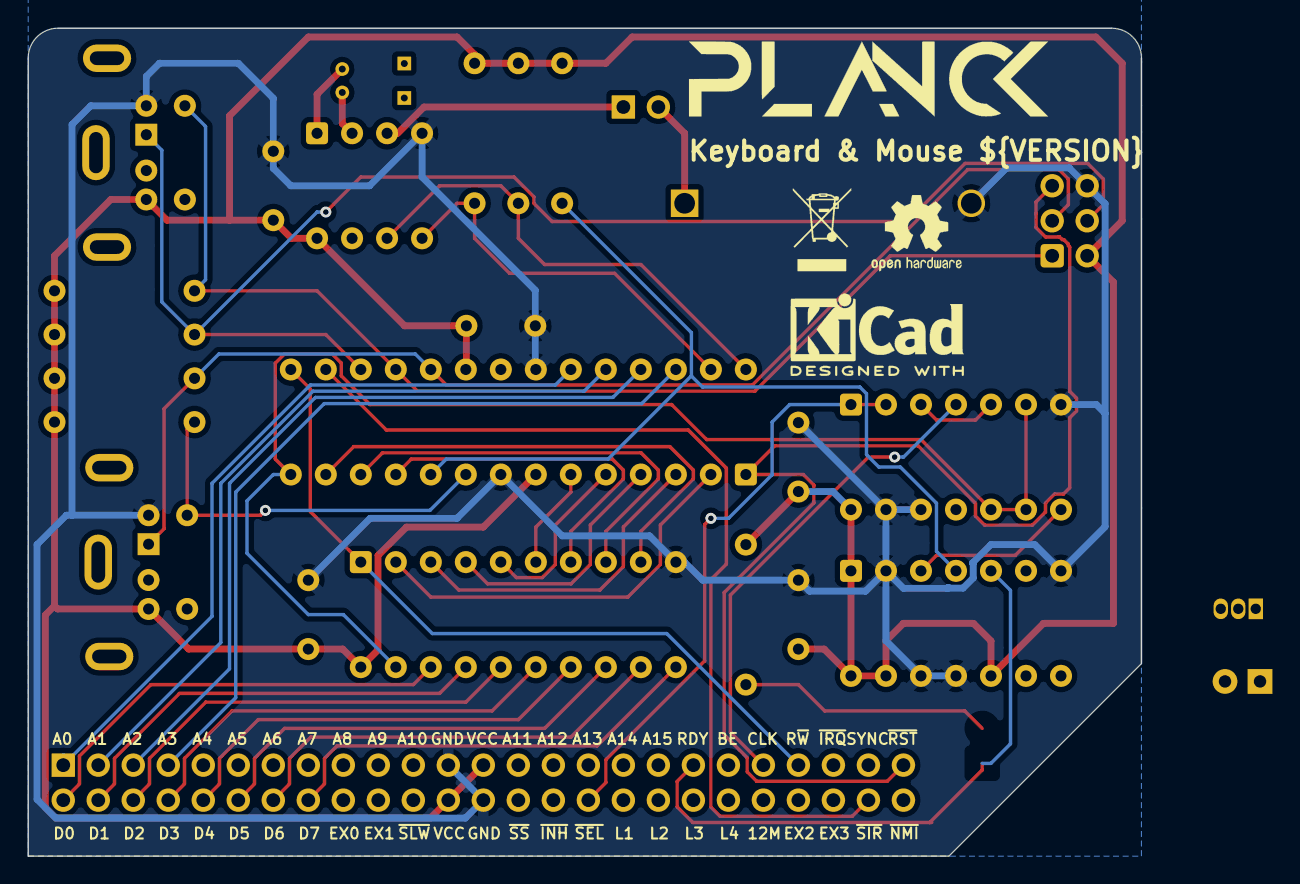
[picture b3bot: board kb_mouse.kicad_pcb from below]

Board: 2 copper layers, 80.8 x 60.1 mm, 31 parts (4 on the bottom side), 45 nets.

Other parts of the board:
KEYBOARD: Mini-DIN-6; Connector_Mini-DIN_Female_6Pin_2rows
KICADLOGO: KiCad-Logo2_5mm_SilkScreen
LOGO: LOGO; logo
MOUSE: Mini-DIN-6; Connector_Mini-DIN_Female_6Pin_2rows
OPENHARDWARE: OSHW-Logo2_7.3x6mm_SilkScreen
R8: 10k; R_Axial_DIN0207_L6.3mm_D2.5mm_P10.16mm_Horizontal
WASTE: WEEE-Logo_4.2x6mm_SilkScreen

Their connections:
+5V: KEYBOARD.4, MOUSE.4, R8.2; also elsewhere on the board
GND: KEYBOARD.3, MOUSE.3; also elsewhere on the board
KBD CLK: KEYBOARD.5; also elsewhere on the board
KBD DATA: KEYBOARD.1; also elsewhere on the board
MOUSE CLK: MOUSE.5; also elsewhere on the board
MOUSE DATA: MOUSE.1; also elsewhere on the board
RDY_STROBE: R8.1; also elsewhere on the board

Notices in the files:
Hardware/mainboard/mainboard.kicad_pcb:
©Jonathan Foucher 2021
